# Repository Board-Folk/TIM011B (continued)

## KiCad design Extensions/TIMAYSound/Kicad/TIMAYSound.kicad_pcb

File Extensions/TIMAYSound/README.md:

# TIMAYSound

Sound card for the TIM-011 supporting the AY-3-8910 or AY-3-8912 sound generator chip. Featuring 3.5mm stereo line output and a DB-9 pin joystick port.

Note: Fit resistor network NR201 if you have an 'A' type chip, e.g. AY-3-8910A.

## Versions

v1 Initial version

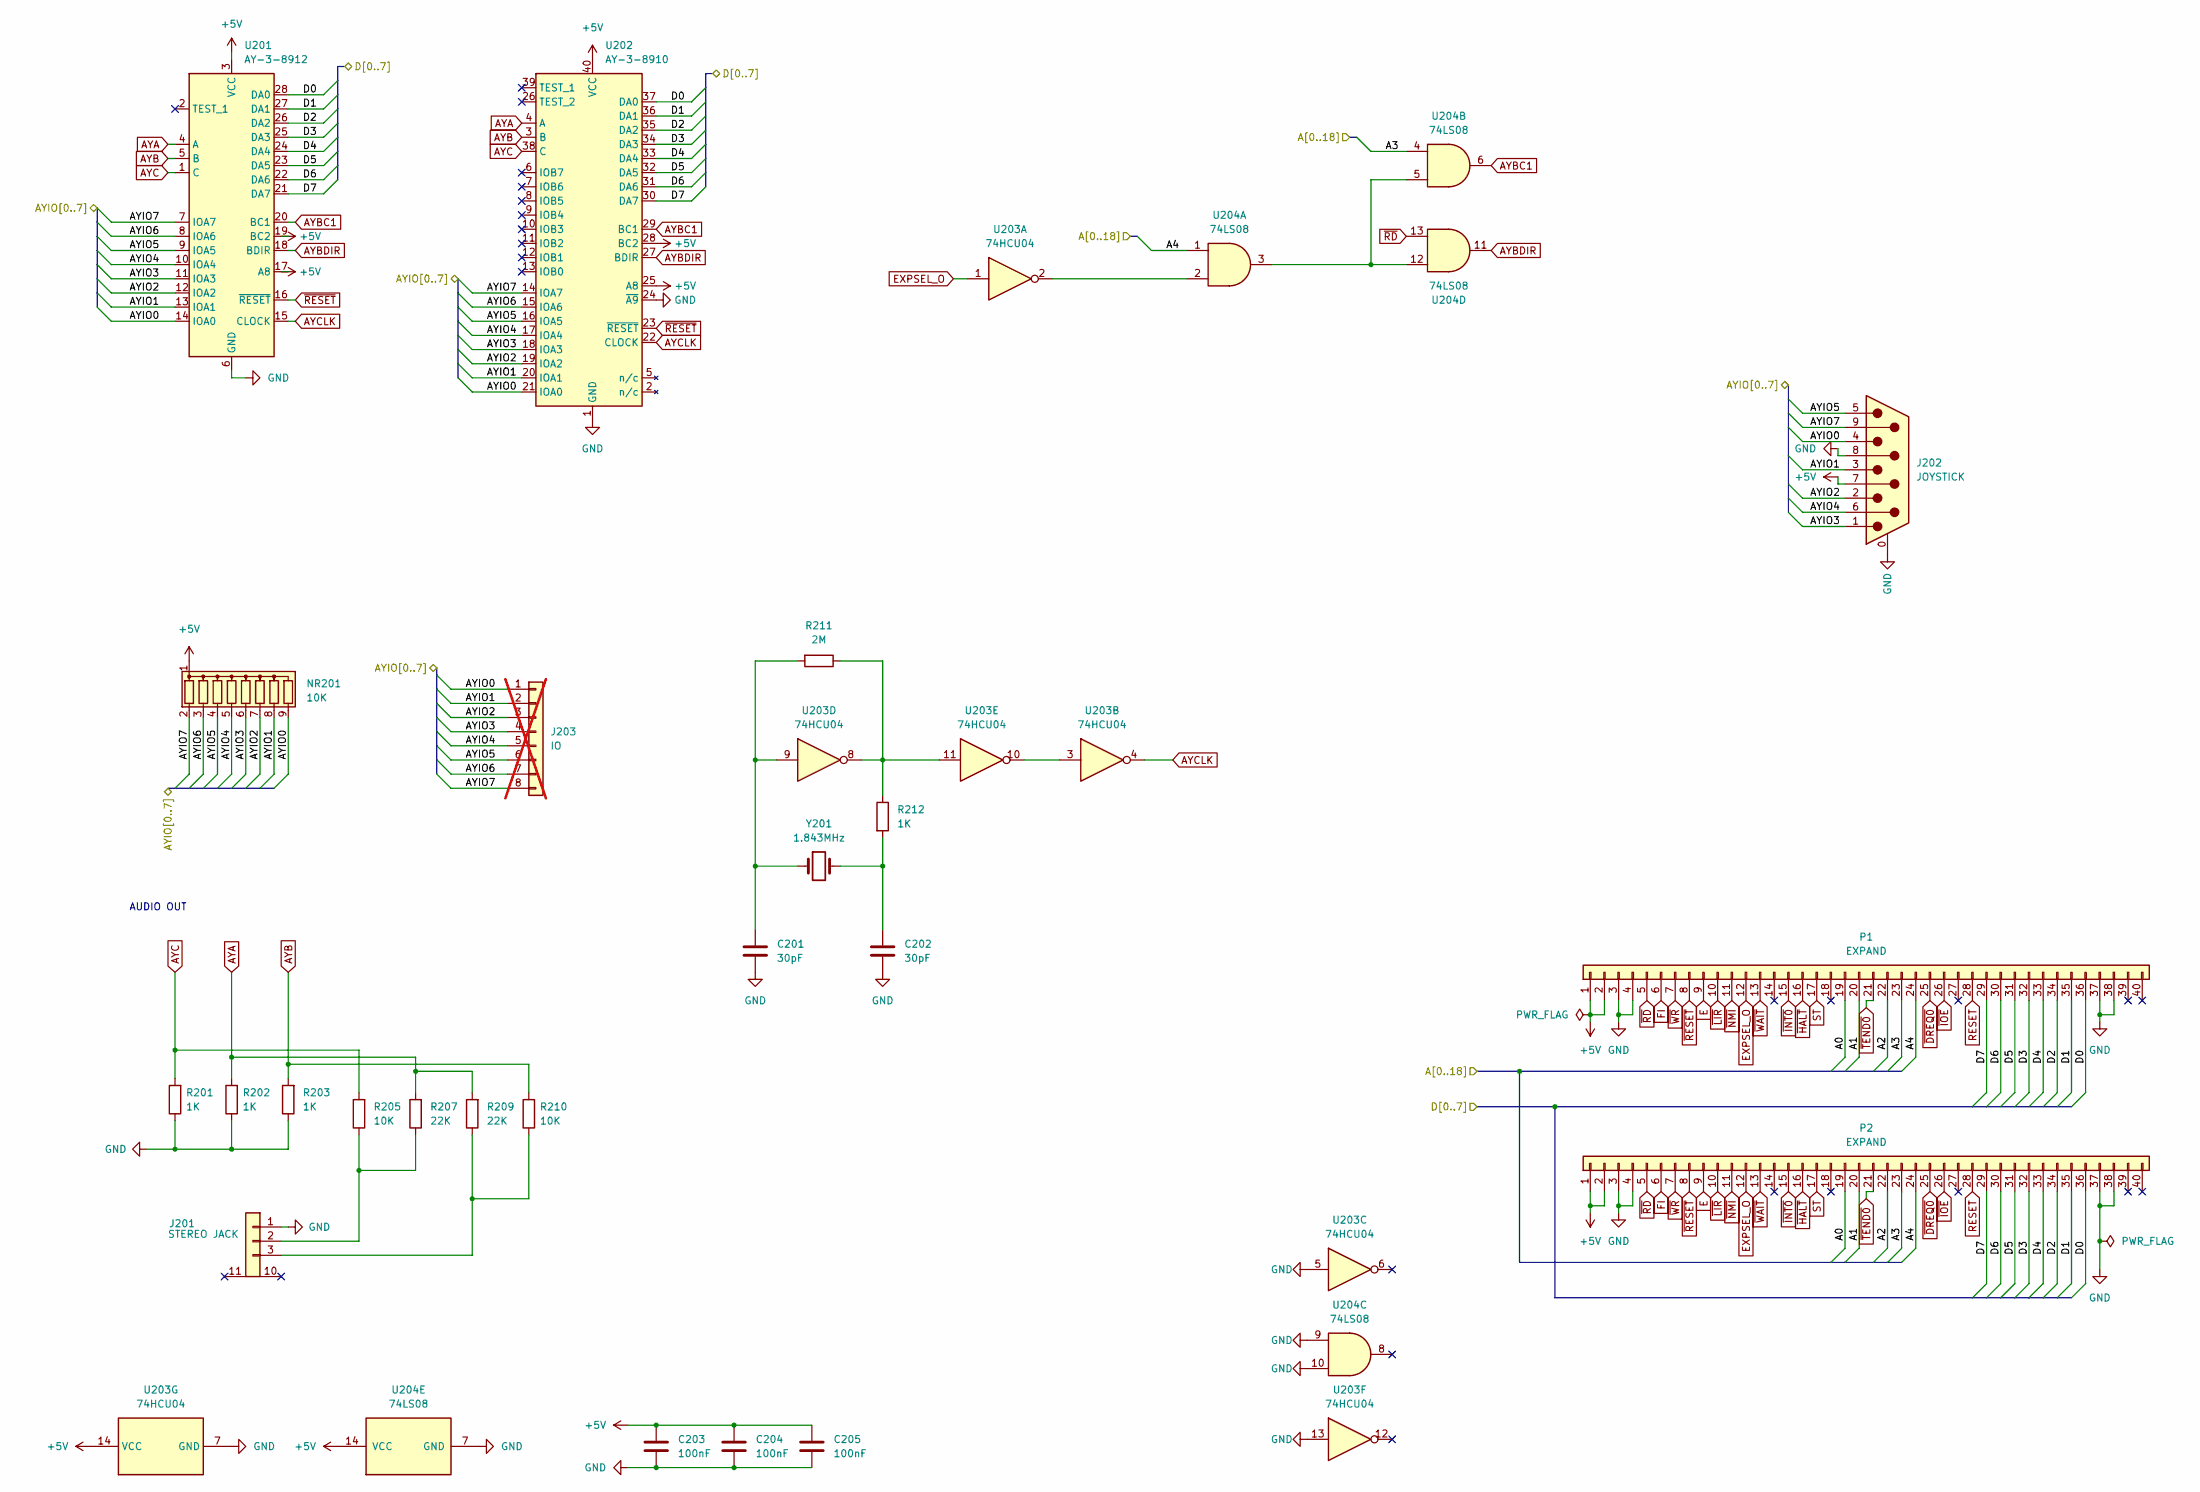
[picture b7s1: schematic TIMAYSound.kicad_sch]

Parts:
C201, C202: 30pF; Ceramic Cap 5.00mm
C203, C204, C205: 100nF; Ceramic Cap 5.00mm
J201: STEREO JACK; STEREO
J202: JOYSTICK
J203: IO; PinHeader_1x08_P2.54mm_Vertical; not fitted
NR201: 10K; R_Array_SIP9
P1, P2: EXPAND; PinHeader_2x20 2.54mm
R201, R202, R203: 1K; Resistor 12.7mm; LCSC C482939
R205, R210: 10K; Resistor 12.7mm; LCSC C84376
R207, R209: 22K; Resistor 12.7mm; LCSC C114565
R211: 2M; Resistor 12.7mm; LCSC C84376
R212: 1K; Resistor 12.7mm; LCSC C84376
U201: AY-3-8912; DIP-28_W15.24mm_Socket
U202: AY-3-8910; DIP-40_W15.24mm_Socket
U203: 74HCU04; DIP-14_W7.62mm
U204: 74LS08; DIP-14_W7.62mm
Y201: 1.843MHz; Crystal_Horizontal

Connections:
+5V: C203.1, C204.1, C205.1, J202.7, NR201.1 (common), P1.1, P1.2, P2.1, P2.2, U201.3 (VCC), U201.17 (A8), U201.19 (BC2), U202.25 (A8), U202.28 (BC2), U202.40 (VCC), U203.14 (VCC), U204.14 (VCC)
/A0: P1.19, P2.19
/A1: P1.20, P2.20
/A2: P1.22, P2.22
/A3: P1.23, P2.23, U204.4
/A4: P1.24, P2.24, U204.1
/AYIO0: J202.4, J203.1, NR201.9 (R8), U201.14 (IOA0), U202.21 (IOA0)
/AYIO1: J202.3, J203.2, NR201.8 (R7), U201.13 (IOA1), U202.20 (IOA1)
/AYIO2: J202.2, J203.3, NR201.7 (R6), U201.12 (IOA2), U202.19 (IOA2)
/AYIO3: J202.1, J203.4, NR201.6 (R5), U201.11 (IOA3), U202.18 (IOA3)
/AYIO4: J202.6, J203.5, NR201.5 (R4), U201.10 (IOA4), U202.17 (IOA4)
/AYIO5: J202.5, J203.6, NR201.4 (R3), U201.9 (IOA5), U202.16 (IOA5)
/AYIO6: J203.7, NR201.3 (R2), U201.8 (IOA6), U202.15 (IOA6)
/AYIO7: J202.9, J203.8, NR201.2 (R1), U201.7 (IOA7), U202.14 (IOA7)
/D0: P1.36, P2.36, U201.28 (DA0), U202.37 (DA0)
/D1: P1.35, P2.35, U201.27 (DA1), U202.36 (DA1)
/D2: P1.34, P2.34, U201.26 (DA2), U202.35 (DA2)
/D3: P1.32, P2.32, U201.25 (DA3), U202.34 (DA3)
/D4: P1.33, P2.33, U201.24 (DA4), U202.33 (DA4)
/D5: P1.31, P2.31, U201.23 (DA5), U202.32 (DA5)
/D6: P1.30, P2.30, U201.22 (DA6), U202.31 (DA6)
/D7: P1.29, P2.29, U201.21 (DA7), U202.30 (DA7)
AYA: R202.2, R207.2, R209.2, U201.4 (A), U202.4 (A)
AYB: R203.2, R210.2, U201.5 (B), U202.3 (B)
AYBC1: U201.20 (BC1), U202.29 (BC1), U204.6
AYBDIR: U201.18 (BDIR), U202.27 (BDIR), U204.11
AYC: R201.2, R205.2, U201.1 (C), U202.38 (C)
AYCLK: U201.15 (CLOCK), U202.22 (CLOCK), U203.4
E: P1.9, P2.9
EXPSEL_O: P1.12, P2.12, U203.1
FI: P1.6, P2.6
GND: C201.1, C202.1, C203.2, C204.2, C205.2, J201.1, J202.0 (PAD), J202.8, P1.3, P1.4, P1.37, P1.38, P2.3, P2.4, P2.37, P2.38, R201.1, R202.1, R203.1, U201.6 (GND), U202.1 (GND), U202.24 (~A9), U203.5, U203.7 (GND), U203.13, U204.7 (GND), U204.9, U204.10
unnamed: C201.2, R211.2, U203.9, Y201.1
unnamed: C202.2, R212.2, Y201.2
unnamed: J201.3 (Ground), R209.1, R210.1
unnamed: J201.2, R205.1, R207.1
unnamed: R211.1, R212.1, U203.8, U203.11
unnamed: U203.2, U204.2
unnamed: U203.3, U203.10
unnamed: U204.3, U204.5, U204.12
RESET: P1.28, P2.28
ST: P1.17, P2.17
~DREQ0: P1.25, P2.25
~HALT: P1.16, P2.16
~INT0: P1.15, P2.15
~IOE: P1.26, P2.26
~LIR: P1.10, P2.10
~NMI: P1.11, P2.11
~RD: P1.5, P2.5, U204.13
~RESET: P1.8, P2.8, U201.16 (~RESET), U202.23 (~RESET)
~TEND0: P1.21, P2.21
~WAIT: P1.13, P2.13
~WR: P1.7, P2.7

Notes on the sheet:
AUDIO OUT

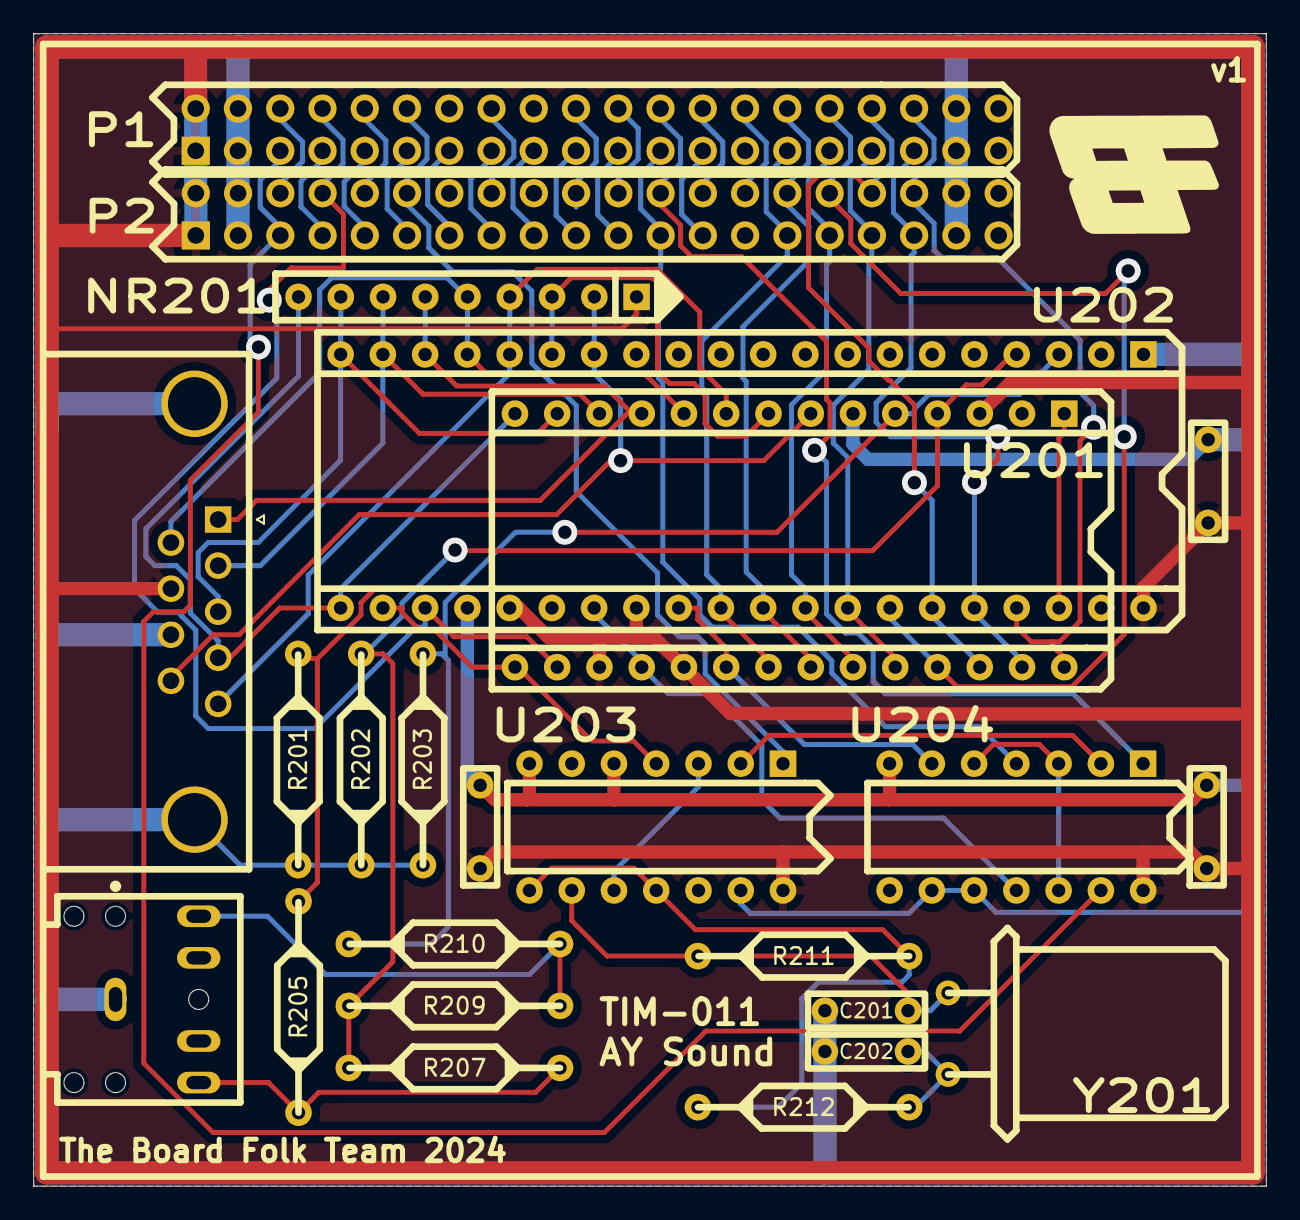
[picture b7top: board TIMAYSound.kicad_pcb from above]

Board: 2 copper layers, 74.1 x 69.3 mm, 24 parts (0 on the bottom side), 53 nets.

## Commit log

2024-03-24 Baseline
2024-03-26 Initial Version 1 BOM
2024-04-03 Remove C42 Label
2024-04-04 Fix J4, J5.
2024-04-05 Updates
    Moved C6 and C7 to stop chances of shorting with crystals. U15 silkscreen designator moved.
2024-04-05 Updates
    Fixed Zoltan credit. Made octagons symmetrical.
2024-04-06 Fixed U18 to LS20
2024-04-06 Revert "Fixed U18 to LS20"
    This reverts commit cd711aa80148ada8cd234e791330af1c79c45b27.
2024-04-06 U18 correction, ROM A13 ground, DB25 mouting hole fix, remove H9, Credits Update
2024-04-08 JMP4 Floppy Ready/Disk Change Mod
2024-04-09 Upload TIMPS2Key v0
2024-04-11 Move thanks to top right
2024-04-11 Tidy up / revision on back.
2024-04-11 Readme updates etc
2024-04-11 Readme updates
2024-04-11 Added TIMAYSound
2024-04-11 Update readmes
2024-04-12 v1.1 Upload
2024-04-12 Readme Updates, Add Marko's Link
2024-04-18 Update Readme (Marko's Blog) and iBOM Update
2024-11-16 v1.3 Initial Notes
2024-11-16 v1.3 BOM
2024-11-16 v1.3 Import
2024-11-16 Jumper Settings
2024-11-16 v1.3 ROM
2024-11-16 PS/2 Keyboard revisions v1 (Nano) and v2 (328) and i2c board.
2024-11-16 Add tim011_video_fix
2024-11-16 TIMIDE
2024-12-14 v1.3.1 Silkscreen Update
2024-12-15 TIMPS2KeyMiniv1.1
